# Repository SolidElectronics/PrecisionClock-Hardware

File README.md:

# PrecisionClock-Hardware
Alternate board designs for [mitxela/PrecisionClockMkII](https://github.com/mitxela/PrecisionClockMkII)

[0.56 inch x 18](/0.56%20inch%20x%2018) is a fully compatible version of the original design, but using the more readily available 0.56" displays.

[two row tenths v2](/two%20row%20tenths%20v2/) is a new design that requires modified firmware which you can get from [SolidElectronics/PrecisionClockMkII](https://github.com/SolidElectronics/PrecisionClockMkII).  That firmware supports both the original and new board versions (select using the #define statements).  The major changes included in this board are:

- Stacked date above time.  Date uses 0.56" LEDs and time uses 0.8" LEDs with 3mm LEDs for colons.

- USB-C power input, with footprints for mounting the connector on the side or the bottom.

- Dedicated holes for antenna mount, and I included STLs for the common ceramic antenna included with the GPS modules, and an SMA-mount if you'd prefer to use that.  I also added optional covers that can go over the colon indicators to make it look a bit more finished.

- Use surface-mount components wherever possible (not the AVR or MAX7219s because I already had the DIP versions)

- Switched non-segment indicators (colons and GMT/BST indicators) to use dedicated output pins on the MCU.  I found that driving anything other than the segments from the MAX7219 caused ghosting on the associated digits, and there wasn't a way to reduce the LED brightness that worked.

- Implemented digital brightness control.  The analog brightness control was great in theory but I couldn't get it to drive the LEDs at a level I was happy with, it would either be too bright or they'd go out entirely in a dark environment.  This probably could have been resolved by picking the correct transistors, LDR, and resistor values, but it was too much of a pain to re-solder them every time.

  Some concessions had to be made here due to the hardware limitations of the ATTiny2313, there is no ADC and only one available PWM output.  The LDR now uses the analog comparator to switch beteen high and low brightness, not a smooth gradient.  The non-segment indicators are PWM-driven through a 74AHCT125 so their brightness can be set independently from the main display, and the main display now uses the built-in dimming function from the MAX7219.  All of the parameters are tunable in the firmware, and there are potentiometers on the back to set the dimming switchover point and the overall date and time brightness levels.

It took a lot more work than I expected to get it to this point, and it was probably the most trace-dense board I've made, but overall I'm happy with how it turned out and it's now a permanent fixture in my office.

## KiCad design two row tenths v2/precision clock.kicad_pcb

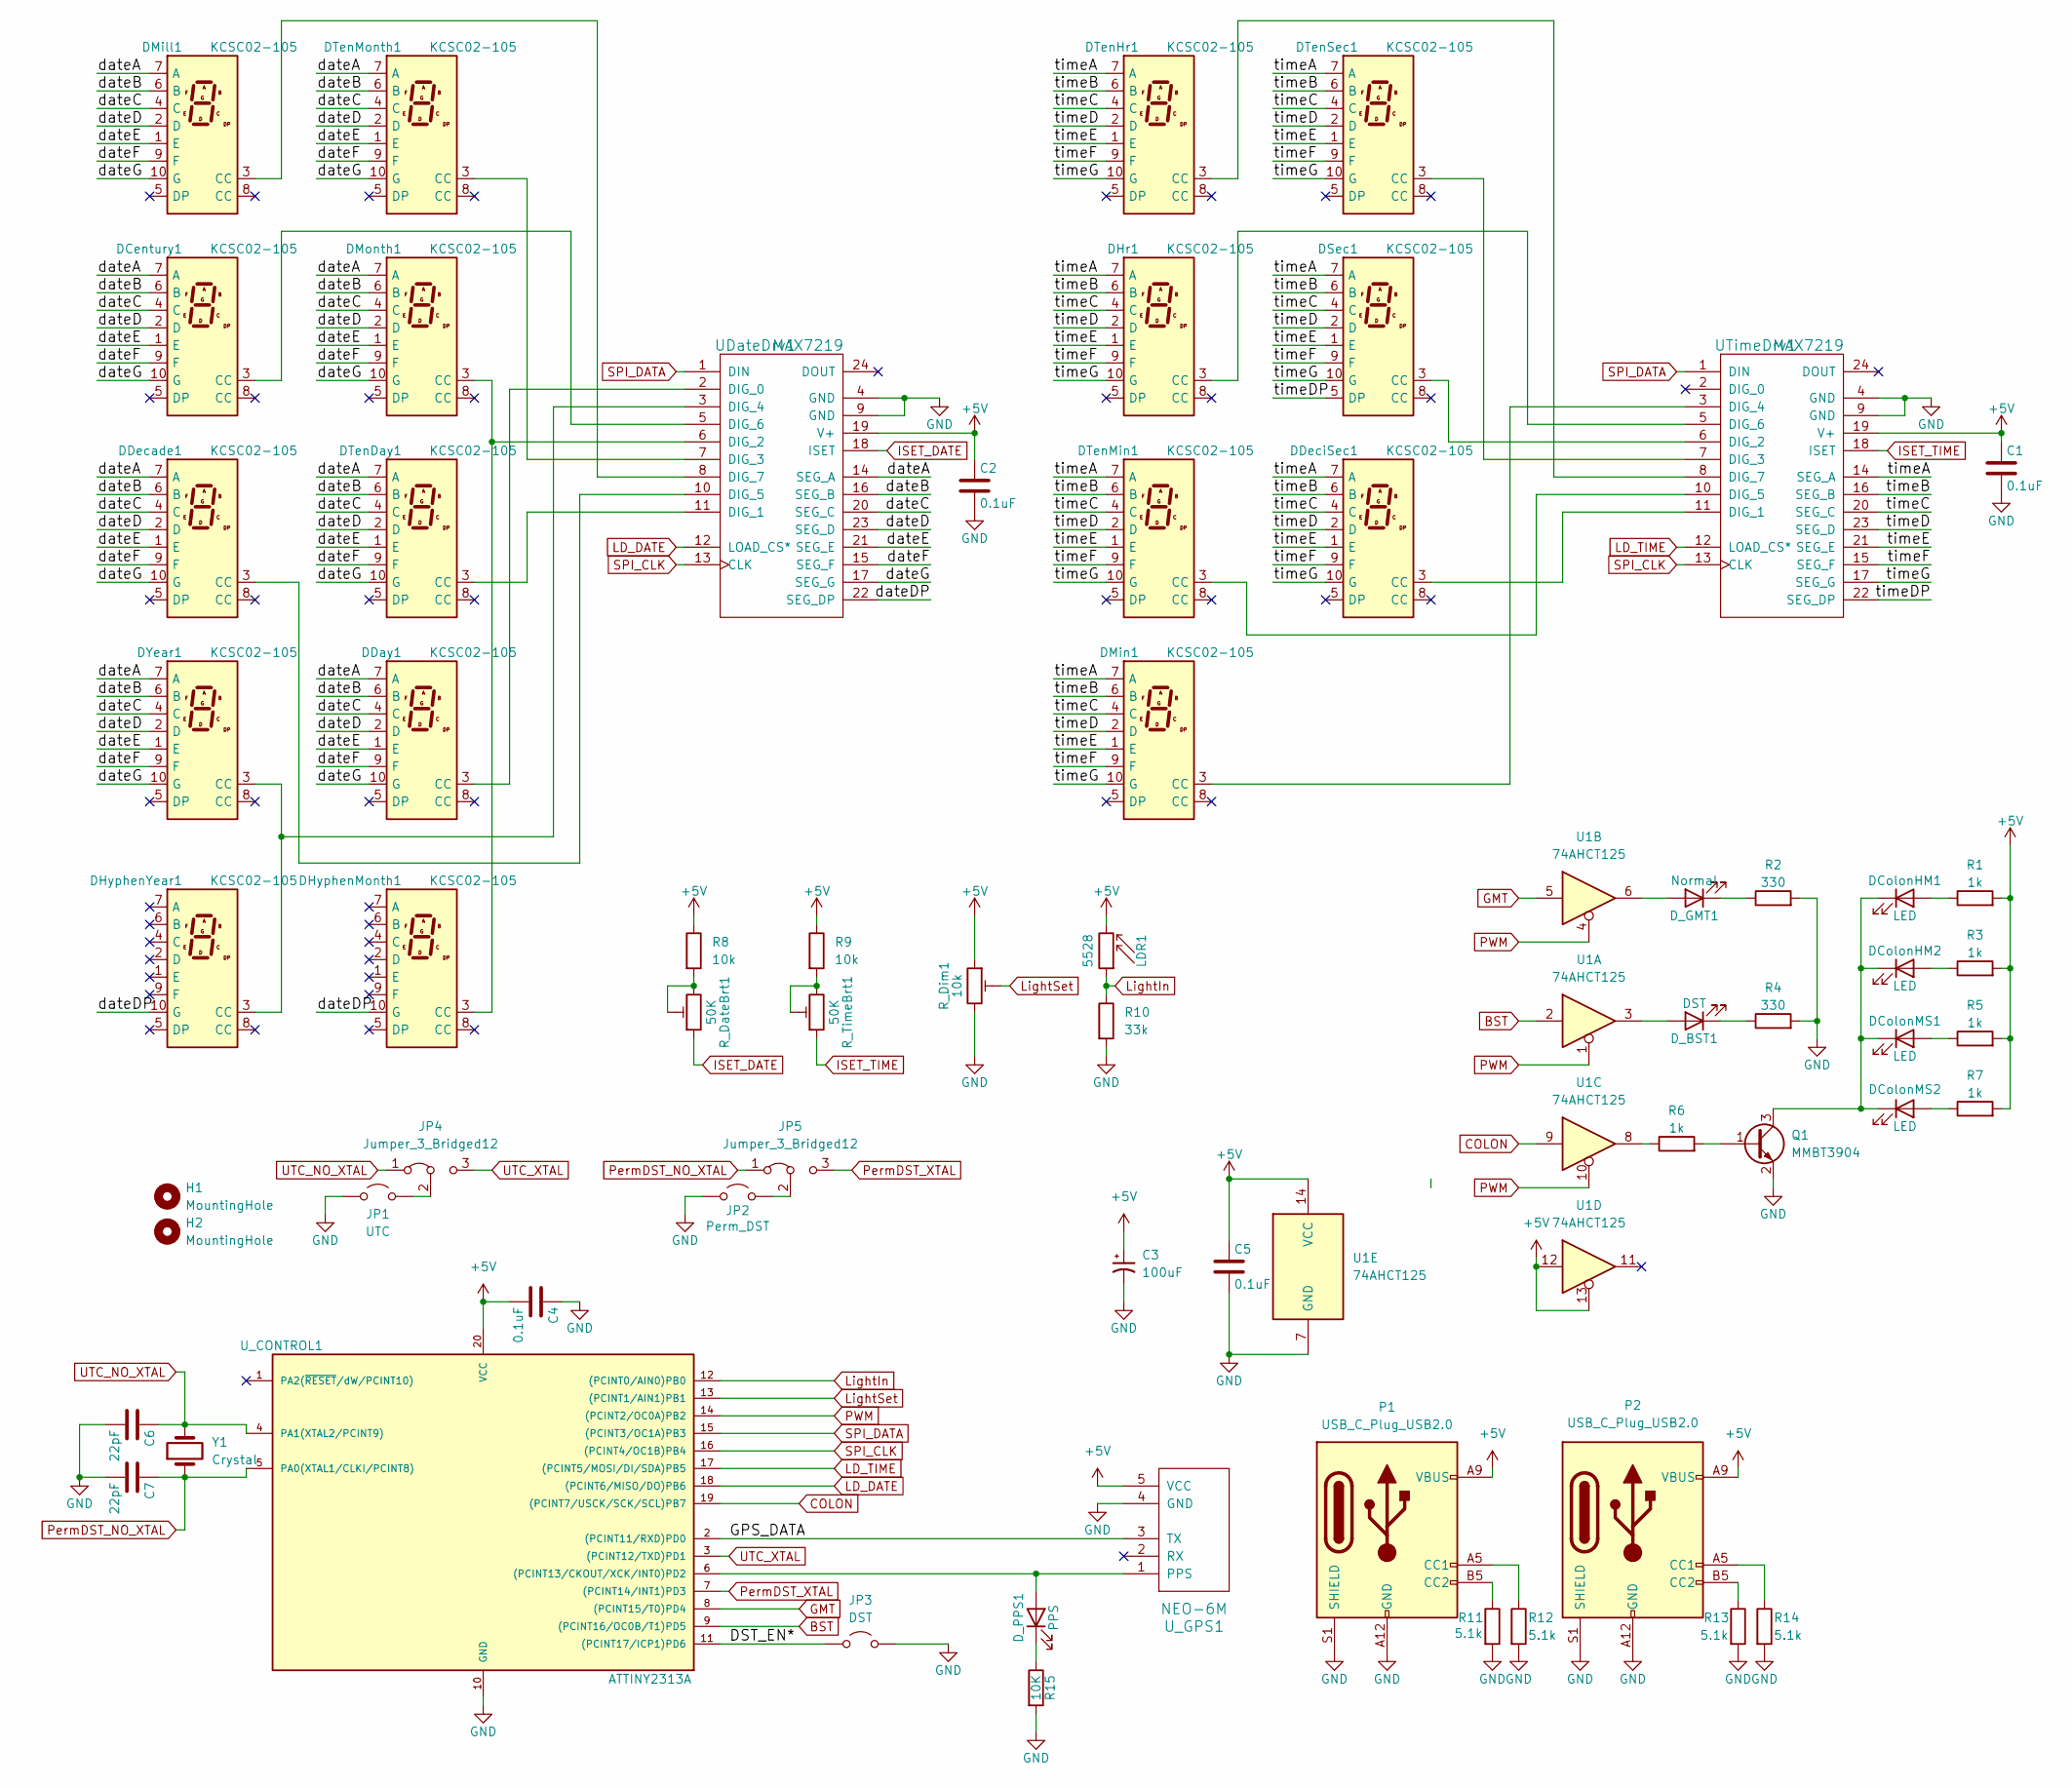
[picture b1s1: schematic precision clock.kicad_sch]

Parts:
C1, C2, C4, C5: 0.1uF; C_1206_3216Metric
C3: 100uF; CP_Radial_D6.3mm_P2.50mm
C6, C7: 22pF; C_1206_3216Metric
DCentury1: KCSC02-105; 7seg0.56CC
DColonHM1, DColonHM2: LED; LED_D5.0mm
DColonMS1, DColonMS2: LED; LED_D5.0mm
DDay1: KCSC02-105; 7seg0.56CC
DDecade1: KCSC02-105; 7seg0.56CC
DDeciSec1: KCSC02-105; 7seg0.8CC
DHr1: KCSC02-105; 7seg0.8CC
DHyphenMonth1: KCSC02-105; 7seg0.56CC
DHyphenYear1: KCSC02-105; 7seg0.56CC
DMill1: KCSC02-105; 7seg0.56CC
DMin1: KCSC02-105; 7seg0.8CC
DMonth1: KCSC02-105; 7seg0.56CC
DSec1: KCSC02-105; 7seg0.8CC
DTenDay1: KCSC02-105; 7seg0.56CC
DTenHr1: KCSC02-105; 7seg0.8CC
DTenMin1: KCSC02-105; 7seg0.8CC
DTenMonth1: KCSC02-105; 7seg0.56CC
DTenSec1: KCSC02-105; 7seg0.8CC
DYear1: KCSC02-105; 7seg0.56CC
D_BST1: DST; LED_1206_3216Metric
D_GMT1: Normal; LED_1206_3216Metric
D_PPS1: PPS; LED_1206_3216Metric
H1, H2: MountingHole; MountingHole_3.2mm_M3
JP1: UTC; PinHeader_1x02_P2.54mm_Vertical
JP2: Perm_DST; PinHeader_1x02_P2.54mm_Vertical
JP3: DST; PinHeader_1x02_P2.54mm_Vertical
JP4, JP5: Jumper_3_Bridged12; SolderJumper-3_P1.3mm_Bridged12_Pad1.0x1.5mm
LDR1: 5528; R_LDR_4.9x4.2mm_P2.54mm_Vertical
P1, P2: USB_C_Plug_USB2.0; USB_C_Receptacle_HRO_TYPE-C-31-M-17
Q1: MMBT3904; SOT-23
R1, R3, R5, R6, R7: 1k; R_1206_3216Metric
R2, R4: 330; R_1206_3216Metric
R8, R9: 10k; R_1206_3216Metric
R10: 33k; R_1206_3216Metric
R11, R12, R13, R14: 5.1k; R_1206_3216Metric
R15: 10K; R_1206_3216Metric
R_DateBrt1: 50K; Potentiometer_Piher_PT-6-V_Vertical
R_Dim1: 10k; Potentiometer_Piher_PT-6-V_Vertical
R_TimeBrt1: 50K; Potentiometer_Piher_PT-6-V_Vertical
U1: 74AHCT125; SOIC-14_3.9x8.7mm_P1.27mm
UDateDrv1: MAX7219; DIP-24_W7.62mm
UTimeDrv1: MAX7219; DIP-24_W7.62mm
U_CONTROL1: ATTINY2313A; DIP-20_W7.62mm
U_GPS1: NEO-6M; ublox_GPS
Y1: Crystal; Crystal_SMD_HC49-SD

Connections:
+5V: C1.1, C2.1, C3.1, C4.2, C5.1, LDR1.2, P1.A9 (VBUS), P1.B9 (VBUS), P2.A9 (VBUS), P2.B9 (VBUS), R1.2, R3.2, R5.2, R7.2, R8.1, R9.1, R_Dim1.1, U1.12, U1.13, U1.14 (VCC), UDateDrv1.19 (V+), UTimeDrv1.19 (V+), U_CONTROL1.20 (VCC), U_GPS1.5 (VCC)
/DST_EN*: JP3.1 (A), U_CONTROL1.11 ((PCINT17/ICP1)PD6)
/GPS_DATA: U_CONTROL1.2 ((PCINT11/RXD)PD0), U_GPS1.3 (TX)
/dateA: DCentury1.7 (A), DDay1.7 (A), DDecade1.7 (A), DMill1.7 (A), DMonth1.7 (A), DTenDay1.7 (A), DTenMonth1.7 (A), DYear1.7 (A), UDateDrv1.14 (SEG_A)
/dateB: DCentury1.6 (B), DDay1.6 (B), DDecade1.6 (B), DMill1.6 (B), DMonth1.6 (B), DTenDay1.6 (B), DTenMonth1.6 (B), DYear1.6 (B), UDateDrv1.16 (SEG_B)
/dateC: DCentury1.4 (C), DDay1.4 (C), DDecade1.4 (C), DMill1.4 (C), DMonth1.4 (C), DTenDay1.4 (C), DTenMonth1.4 (C), DYear1.4 (C), UDateDrv1.20 (SEG_C)
/dateD: DCentury1.2 (D), DDay1.2 (D), DDecade1.2 (D), DMill1.2 (D), DMonth1.2 (D), DTenDay1.2 (D), DTenMonth1.2 (D), DYear1.2 (D), UDateDrv1.23 (SEG_D)
/dateDP: DHyphenMonth1.10 (G), DHyphenYear1.10 (G), UDateDrv1.22 (SEG_DP)
/dateE: DCentury1.1 (E), DDay1.1 (E), DDecade1.1 (E), DMill1.1 (E), DMonth1.1 (E), DTenDay1.1 (E), DTenMonth1.1 (E), DYear1.1 (E), UDateDrv1.21 (SEG_E)
/dateF: DCentury1.9 (F), DDay1.9 (F), DDecade1.9 (F), DMill1.9 (F), DMonth1.9 (F), DTenDay1.9 (F), DTenMonth1.9 (F), DYear1.9 (F), UDateDrv1.15 (SEG_F)
/dateG: DCentury1.10 (G), DDay1.10 (G), DDecade1.10 (G), DMill1.10 (G), DMonth1.10 (G), DTenDay1.10 (G), DTenMonth1.10 (G), DYear1.10 (G), UDateDrv1.17 (SEG_G)
/timeA: DDeciSec1.7 (A), DHr1.7 (A), DMin1.7 (A), DSec1.7 (A), DTenHr1.7 (A), DTenMin1.7 (A), DTenSec1.7 (A), UTimeDrv1.14 (SEG_A)
/timeB: DDeciSec1.6 (B), DHr1.6 (B), DMin1.6 (B), DSec1.6 (B), DTenHr1.6 (B), DTenMin1.6 (B), DTenSec1.6 (B), UTimeDrv1.16 (SEG_B)
/timeC: DDeciSec1.4 (C), DHr1.4 (C), DMin1.4 (C), DSec1.4 (C), DTenHr1.4 (C), DTenMin1.4 (C), DTenSec1.4 (C), UTimeDrv1.20 (SEG_C)
/timeD: DDeciSec1.2 (D), DHr1.2 (D), DMin1.2 (D), DSec1.2 (D), DTenHr1.2 (D), DTenMin1.2 (D), DTenSec1.2 (D), UTimeDrv1.23 (SEG_D)
/timeDP: DSec1.5 (DP), UTimeDrv1.22 (SEG_DP)
/timeE: DDeciSec1.1 (E), DHr1.1 (E), DMin1.1 (E), DSec1.1 (E), DTenHr1.1 (E), DTenMin1.1 (E), DTenSec1.1 (E), UTimeDrv1.21 (SEG_E)
/timeF: DDeciSec1.9 (F), DHr1.9 (F), DMin1.9 (F), DSec1.9 (F), DTenHr1.9 (F), DTenMin1.9 (F), DTenSec1.9 (F), UTimeDrv1.15 (SEG_F)
/timeG: DDeciSec1.10 (G), DHr1.10 (G), DMin1.10 (G), DSec1.10 (G), DTenHr1.10 (G), DTenMin1.10 (G), DTenSec1.10 (G), UTimeDrv1.17 (SEG_G)
BST: U1.2, U_CONTROL1.9 ((PCINT16/OC0B/T1)PD5)
COLON: U1.9, U_CONTROL1.19 ((PCINT7/USCK/SCK/SCL)PB7)
GMT: U1.5, U_CONTROL1.8 ((PCINT15/T0)PD4)
GND: C1.2, C2.2, C3.2, C4.1, C5.2, C6.2, C7.2, JP1.2 (B), JP2.2 (B), JP3.2 (B), P1.A12 (GND), P1.B12 (GND), P1.S1 (SHIELD), P2.A12 (GND), P2.B12 (GND), P2.S1 (SHIELD), Q1.2 (E), R2.2, R4.2, R10.2, R11.2, R12.2, R13.2, R14.2, R15.2, R_Dim1.3, U1.7 (GND), UDateDrv1.4 (GND), UDateDrv1.9 (GND), UTimeDrv1.4 (GND), UTimeDrv1.9 (GND), U_CONTROL1.10 (GND), U_GPS1.4 (GND)
ISET_DATE: R_DateBrt1.1, UDateDrv1.18 (ISET)
ISET_TIME: R_TimeBrt1.1, UTimeDrv1.18 (ISET)
LD_DATE: UDateDrv1.12 (LOAD_CS*), U_CONTROL1.18 ((PCINT6/MISO/DO)PB6)
LD_TIME: UTimeDrv1.12 (LOAD_CS*), U_CONTROL1.17 ((PCINT5/MOSI/DI/SDA)PB5)
LightIn: LDR1.1, R10.1, U_CONTROL1.12 ((PCINT0/AIN0)PB0)
LightSet: R_Dim1.2, U_CONTROL1.13 ((PCINT1/AIN1)PB1)
unnamed: DColonHM1.2 (A), R1.1
unnamed: DColonHM1.1 (K), DColonHM2.1 (K), DColonMS1.1 (K), DColonMS2.1 (K), Q1.3 (C)
unnamed: DColonHM2.2 (A), R3.1
unnamed: DColonMS1.2 (A), R5.1
unnamed: DColonMS2.2 (A), R7.1
unnamed: D_BST1.2 (A), U1.3
unnamed: D_BST1.1 (K), R4.1
unnamed: D_GMT1.2 (A), U1.6
unnamed: D_GMT1.1 (K), R2.1
unnamed: D_PPS1.2 (A), U_CONTROL1.6 ((PCINT13/CKOUT/XCK/INT0)PD2), U_GPS1.1 (PPS)
unnamed: D_PPS1.1 (K), R15.1
unnamed: JP1.1 (A), JP4.2 (C)
unnamed: JP2.1 (A), JP5.2 (C)
unnamed: P1.A5 (CC1), R12.1
unnamed: P1.B5 (CC2), R11.1
unnamed: P2.A5 (CC1), R14.1
unnamed: P2.B5 (CC2), R13.1
unnamed: Q1.1 (B), R6.2
unnamed: R6.1, U1.8
unnamed: R8.2, R_DateBrt1.2, R_DateBrt1.3
unnamed: R9.2, R_TimeBrt1.2, R_TimeBrt1.3
unnamed: DDay1.3 (CC), UDateDrv1.2 (DIG_0)
unnamed: DTenDay1.3 (CC), UDateDrv1.11 (DIG_1)
unnamed: DHyphenMonth1.3 (CC), DMonth1.3 (CC), UDateDrv1.6 (DIG_2)
unnamed: DTenMonth1.3 (CC), UDateDrv1.7 (DIG_3)
unnamed: DHyphenYear1.3 (CC), DYear1.3 (CC), UDateDrv1.3 (DIG_4)
unnamed: DDecade1.3 (CC), UDateDrv1.10 (DIG_5)
unnamed: DCentury1.3 (CC), UDateDrv1.5 (DIG_6)
unnamed: DMill1.3 (CC), UDateDrv1.8 (DIG_7)
unnamed: DDeciSec1.3 (CC), UTimeDrv1.11 (DIG_1)
unnamed: DSec1.3 (CC), UTimeDrv1.6 (DIG_2)
unnamed: DTenSec1.3 (CC), UTimeDrv1.7 (DIG_3)
unnamed: DMin1.3 (CC), UTimeDrv1.3 (DIG_4)
unnamed: DTenMin1.3 (CC), UTimeDrv1.10 (DIG_5)
unnamed: DHr1.3 (CC), UTimeDrv1.5 (DIG_6)
unnamed: DTenHr1.3 (CC), UTimeDrv1.8 (DIG_7)
PWM: U1.1, U1.4, U1.10, U_CONTROL1.14 ((PCINT2/OC0A)PB2)
PermDST_NO_XTAL: C7.1, JP5.1 (A), U_CONTROL1.5 (PA0(XTAL1/CLKI/PCINT8)), Y1.1
PermDST_XTAL: JP5.3 (B), U_CONTROL1.7 ((PCINT14/INT1)PD3)
SPI_CLK: UDateDrv1.13 (CLK), UTimeDrv1.13 (CLK), U_CONTROL1.16 ((PCINT4/OC1B)PB4)
SPI_DATA: UDateDrv1.1 (DIN), UTimeDrv1.1 (DIN), U_CONTROL1.15 ((PCINT3/OC1A)PB3)
UTC_NO_XTAL: C6.1, JP4.1 (A), U_CONTROL1.4 (PA1(XTAL2/PCINT9)), Y1.2
UTC_XTAL: JP4.3 (B), U_CONTROL1.3 ((PCINT12/TXD)PD1)

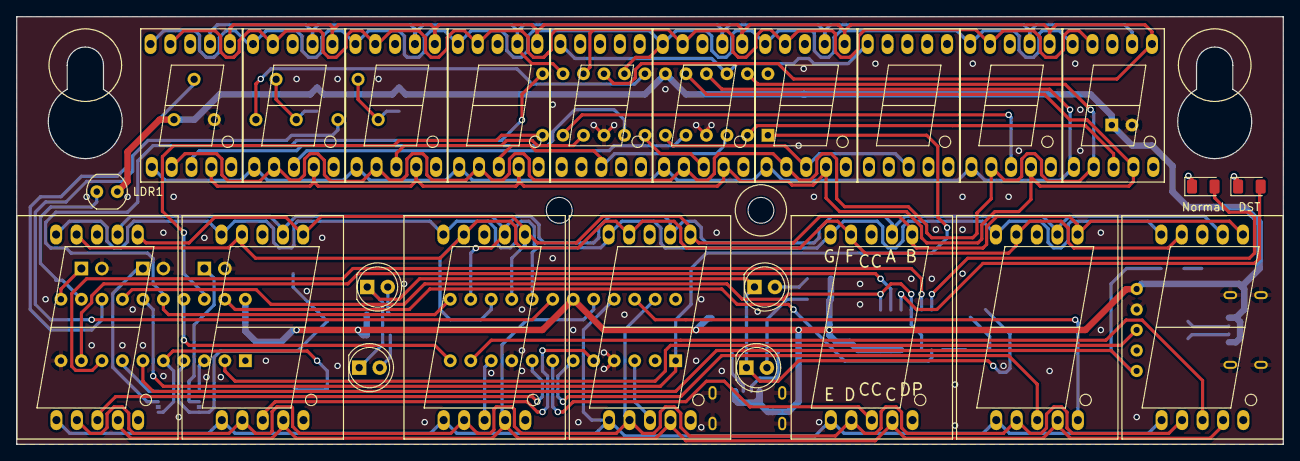
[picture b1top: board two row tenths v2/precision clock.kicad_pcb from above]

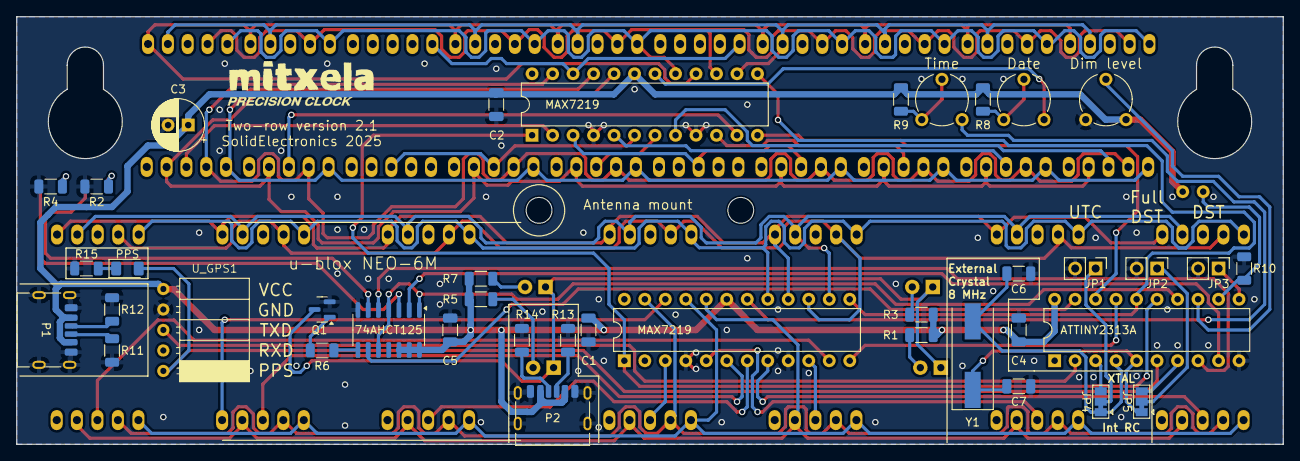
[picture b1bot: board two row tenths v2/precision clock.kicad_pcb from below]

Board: 2 copper layers, 157.0 x 53.0 mm, 66 parts (40 on the bottom side), 72 nets.

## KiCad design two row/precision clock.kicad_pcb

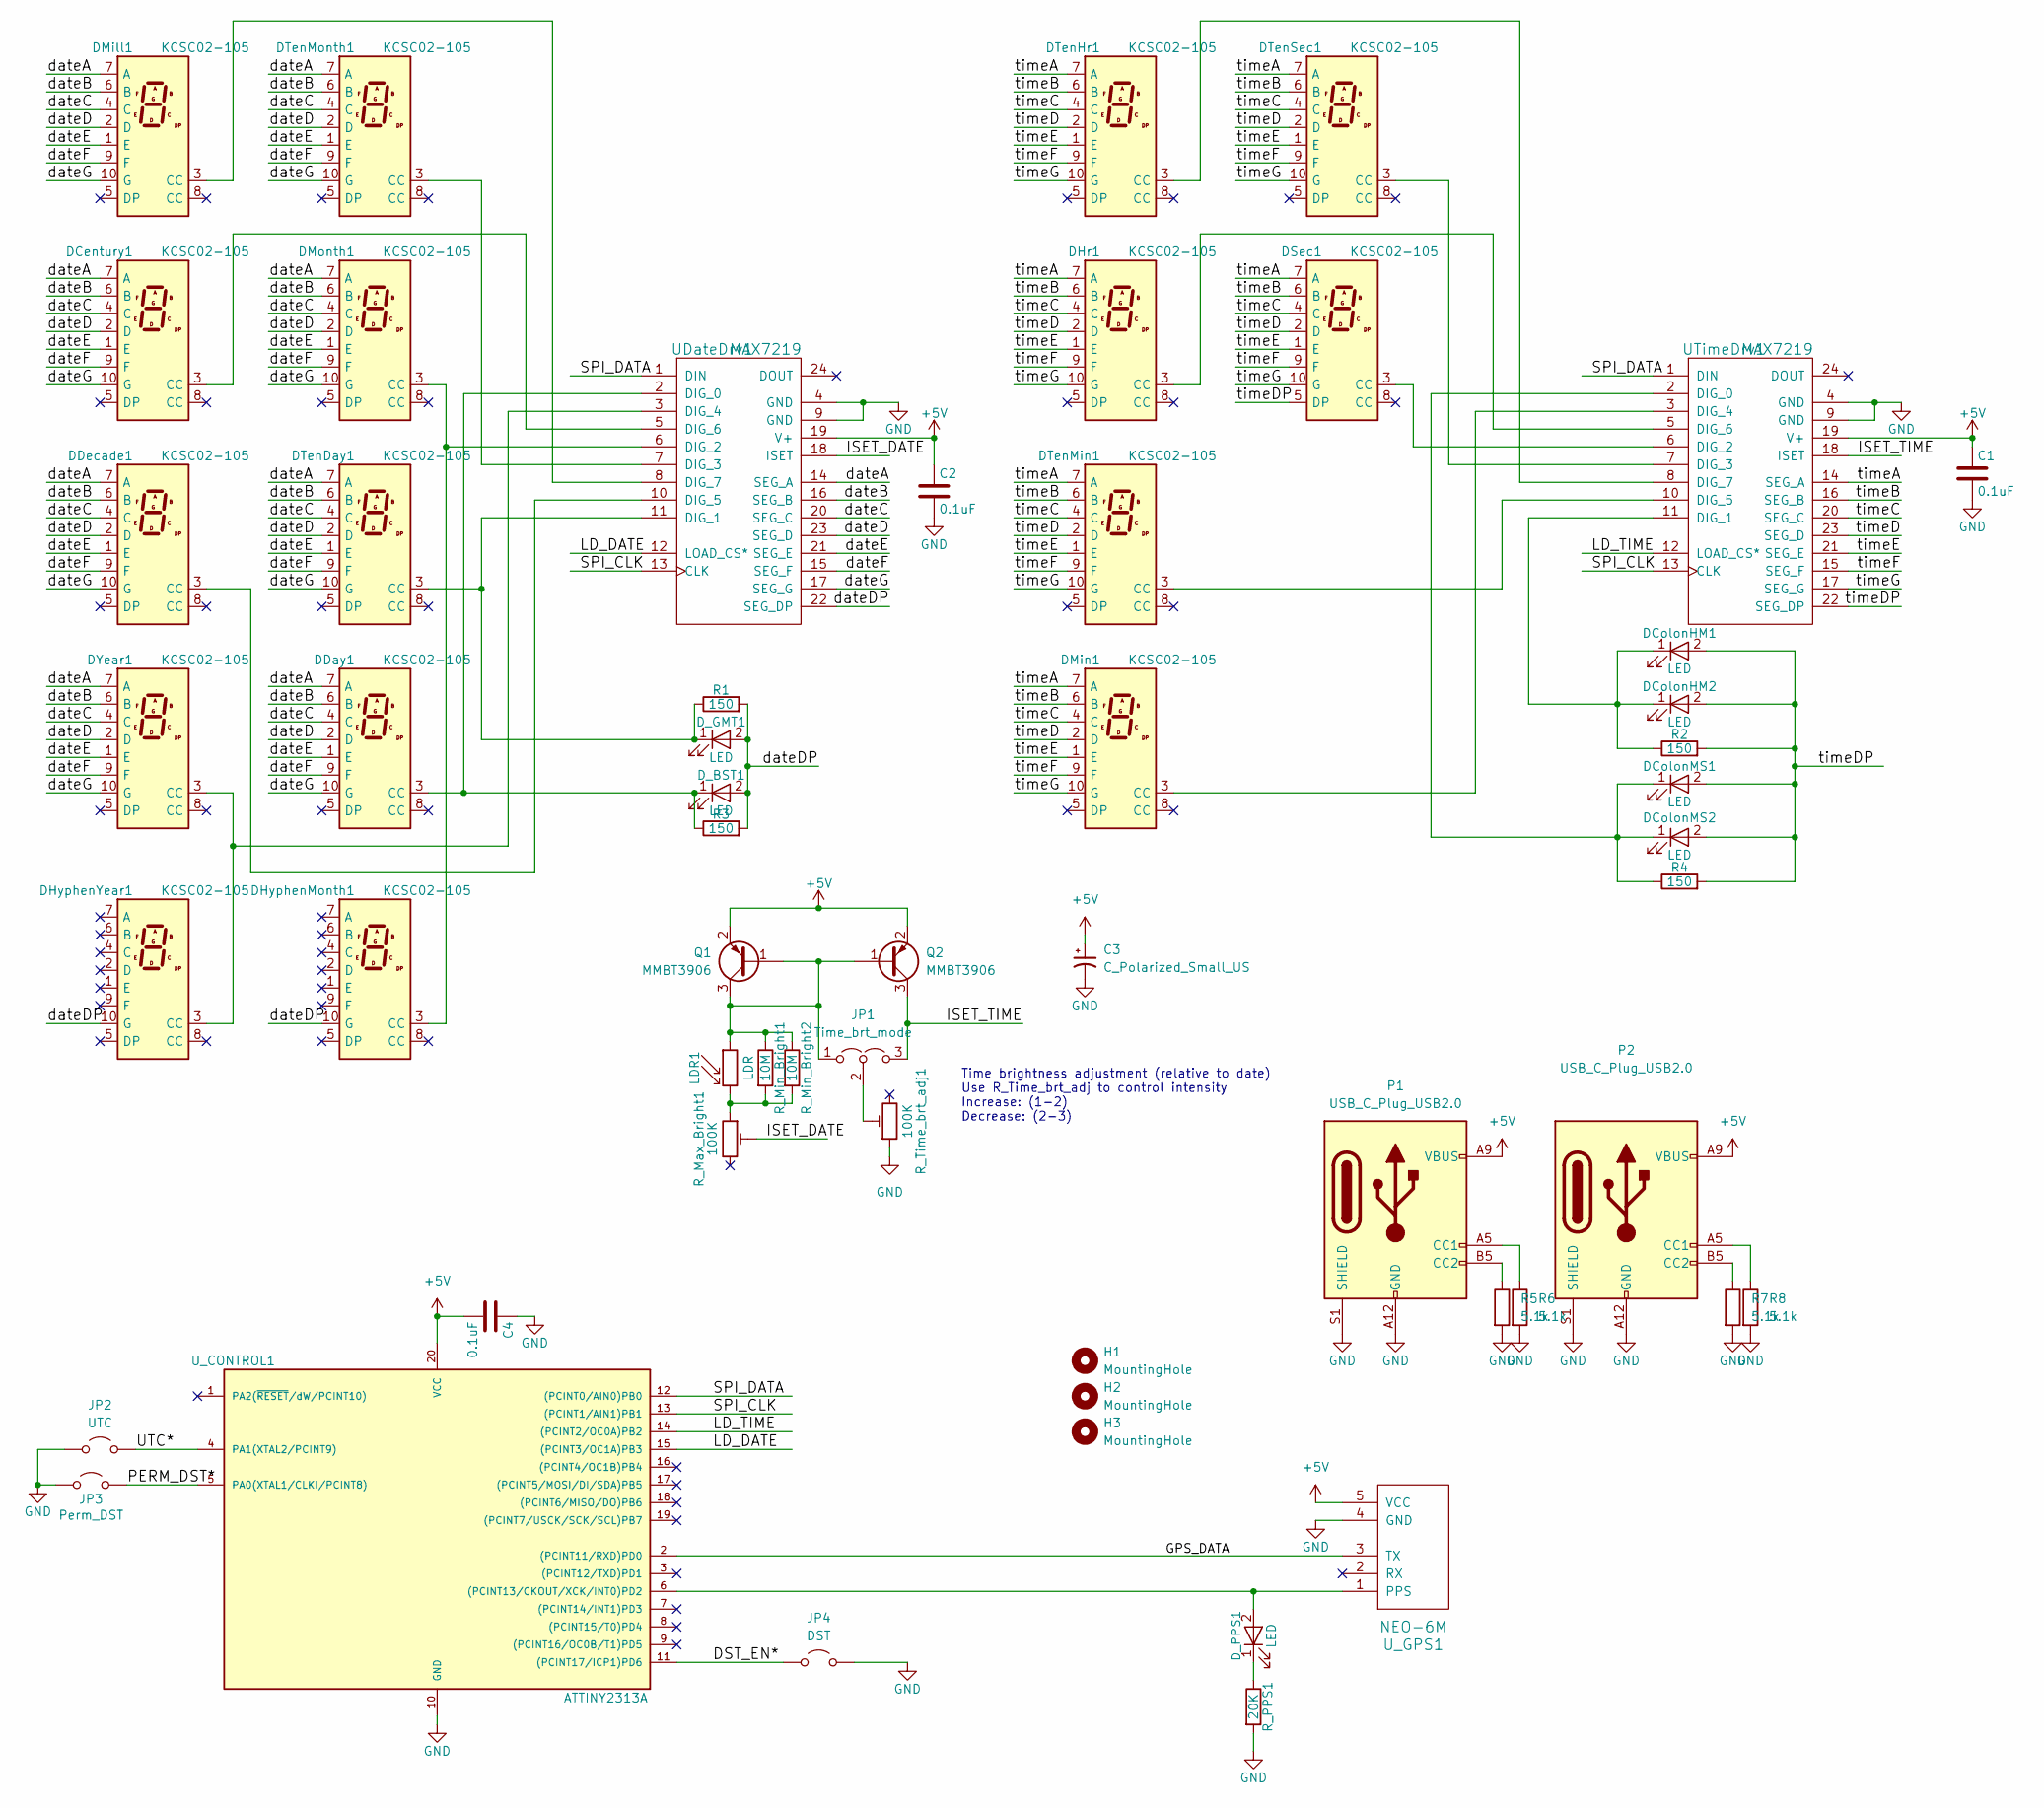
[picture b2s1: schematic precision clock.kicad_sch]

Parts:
C1, C2, C4: 0.1uF; C_1206_3216Metric
C3: C_Polarized_Small_US; CP_Radial_D5.0mm_P2.50mm
DCentury1: KCSC02-105; 7seg0.56CC
DColonHM1, DColonHM2: LED; LED_D5.0mm
DColonMS1, DColonMS2: LED; LED_D5.0mm
DDay1: KCSC02-105; 7seg0.56CC
DDecade1: KCSC02-105; 7seg0.56CC
DHr1: KCSC02-105; 7seg0.8CC
DHyphenMonth1: KCSC02-105; 7seg0.56CC
DHyphenYear1: KCSC02-105; 7seg0.56CC
DMill1: KCSC02-105; 7seg0.56CC
DMin1: KCSC02-105; 7seg0.8CC
DMonth1: KCSC02-105; 7seg0.56CC
DSec1: KCSC02-105; 7seg0.8CC
DTenDay1: KCSC02-105; 7seg0.56CC
DTenHr1: KCSC02-105; 7seg0.8CC
DTenMin1: KCSC02-105; 7seg0.8CC
DTenMonth1: KCSC02-105; 7seg0.56CC
DTenSec1: KCSC02-105; 7seg0.8CC
DYear1: KCSC02-105; 7seg0.56CC
D_BST1: LED; LED_1206_3216Metric
D_GMT1: LED; LED_1206_3216Metric
D_PPS1: LED; LED_1206_3216Metric
H1: MountingHole; MountingHole_3.2mm_M3
H2, H3: MountingHole; MountingHole_2mm
JP1: Time_brt_mode; PinHeader_1x03_P2.54mm_Vertical
JP2: UTC; PinHeader_1x02_P2.54mm_Vertical
JP3: Perm_DST; PinHeader_1x02_P2.54mm_Vertical
JP4: DST; PinHeader_1x02_P2.54mm_Vertical
LDR1: LDR; R_LDR_4.9x4.2mm_P2.54mm_Vertical
P1, P2: USB_C_Plug_USB2.0; USB_C_Receptacle_HRO_TYPE-C-31-M-17
Q1, Q2: MMBT3906; SOT-23
R1, R2, R3, R4: 150; R_1206_3216Metric
R5, R6, R7, R8: 5.1k; R_1206_3216Metric
R_Max_Bright1: 100K; Potentiometer_Piher_PT-6-V_Vertical
R_Min_Bright1: 10M; R_Axial_DIN0207_L6.3mm_D2.5mm_P7.62mm_Horizontal
R_Min_Bright2: 10M; R_1206_3216Metric
R_PPS1: 20K; R_1206_3216Metric
R_Time_brt_adj1: 100K; Potentiometer_Piher_PT-6-V_Vertical
UDateDrv1: MAX7219; DIP-24_W7.62mm
UTimeDrv1: MAX7219; DIP-24_W7.62mm
U_CONTROL1: ATTINY2313A; DIP-20_W7.62mm
U_GPS1: NEO-6M; PinSocket_1x05_P2.54mm_Horizontal

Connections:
+5V: C1.1, C2.1, C3.1, C4.2, P1.A9 (VBUS), P1.B9 (VBUS), P2.A9 (VBUS), P2.B9 (VBUS), Q1.2 (E), Q2.2 (E), UDateDrv1.19 (V+), UTimeDrv1.19 (V+), U_CONTROL1.20 (VCC), U_GPS1.5 (VCC)
/DST_EN*: JP4.1 (A), U_CONTROL1.11 ((PCINT17/ICP1)PD6)
/GPS_DATA: U_CONTROL1.2 ((PCINT11/RXD)PD0), U_GPS1.3 (TX)
/ISET_DATE: R_Max_Bright1.2, UDateDrv1.18 (ISET)
/ISET_TIME: JP1.3 (B), Q2.3 (C), UTimeDrv1.18 (ISET)
/LD_DATE: UDateDrv1.12 (LOAD_CS*), U_CONTROL1.15 ((PCINT3/OC1A)PB3)
/LD_TIME: UTimeDrv1.12 (LOAD_CS*), U_CONTROL1.14 ((PCINT2/OC0A)PB2)
/PERM_DST*: JP3.1 (A), U_CONTROL1.5 (PA0(XTAL1/CLKI/PCINT8))
/SPI_CLK: UDateDrv1.13 (CLK), UTimeDrv1.13 (CLK), U_CONTROL1.13 ((PCINT1/AIN1)PB1)
/SPI_DATA: UDateDrv1.1 (DIN), UTimeDrv1.1 (DIN), U_CONTROL1.12 ((PCINT0/AIN0)PB0)
/UTC*: JP2.1 (A), U_CONTROL1.4 (PA1(XTAL2/PCINT9))
/dateA: DCentury1.7 (A), DDay1.7 (A), DDecade1.7 (A), DMill1.7 (A), DMonth1.7 (A), DTenDay1.7 (A), DTenMonth1.7 (A), DYear1.7 (A), UDateDrv1.14 (SEG_A)
/dateB: DCentury1.6 (B), DDay1.6 (B), DDecade1.6 (B), DMill1.6 (B), DMonth1.6 (B), DTenDay1.6 (B), DTenMonth1.6 (B), DYear1.6 (B), UDateDrv1.16 (SEG_B)
/dateC: DCentury1.4 (C), DDay1.4 (C), DDecade1.4 (C), DMill1.4 (C), DMonth1.4 (C), DTenDay1.4 (C), DTenMonth1.4 (C), DYear1.4 (C), UDateDrv1.20 (SEG_C)
/dateD: DCentury1.2 (D), DDay1.2 (D), DDecade1.2 (D), DMill1.2 (D), DMonth1.2 (D), DTenDay1.2 (D), DTenMonth1.2 (D), DYear1.2 (D), UDateDrv1.23 (SEG_D)
/dateDP: DHyphenMonth1.10 (G), DHyphenYear1.10 (G), D_BST1.2 (A), D_GMT1.2 (A), R1.2, R3.2, UDateDrv1.22 (SEG_DP)
/dateE: DCentury1.1 (E), DDay1.1 (E), DDecade1.1 (E), DMill1.1 (E), DMonth1.1 (E), DTenDay1.1 (E), DTenMonth1.1 (E), DYear1.1 (E), UDateDrv1.21 (SEG_E)
/dateF: DCentury1.9 (F), DDay1.9 (F), DDecade1.9 (F), DMill1.9 (F), DMonth1.9 (F), DTenDay1.9 (F), DTenMonth1.9 (F), DYear1.9 (F), UDateDrv1.15 (SEG_F)
/dateG: DCentury1.10 (G), DDay1.10 (G), DDecade1.10 (G), DMill1.10 (G), DMonth1.10 (G), DTenDay1.10 (G), DTenMonth1.10 (G), DYear1.10 (G), UDateDrv1.17 (SEG_G)
/timeA: DHr1.7 (A), DMin1.7 (A), DSec1.7 (A), DTenHr1.7 (A), DTenMin1.7 (A), DTenSec1.7 (A), UTimeDrv1.14 (SEG_A)
/timeB: DHr1.6 (B), DMin1.6 (B), DSec1.6 (B), DTenHr1.6 (B), DTenMin1.6 (B), DTenSec1.6 (B), UTimeDrv1.16 (SEG_B)
/timeC: DHr1.4 (C), DMin1.4 (C), DSec1.4 (C), DTenHr1.4 (C), DTenMin1.4 (C), DTenSec1.4 (C), UTimeDrv1.20 (SEG_C)
/timeD: DHr1.2 (D), DMin1.2 (D), DSec1.2 (D), DTenHr1.2 (D), DTenMin1.2 (D), DTenSec1.2 (D), UTimeDrv1.23 (SEG_D)
/timeDP: DColonHM1.2 (A), DColonHM2.2 (A), DColonMS1.2 (A), DColonMS2.2 (A), DSec1.5 (DP), R2.2, R4.2, UTimeDrv1.22 (SEG_DP)
/timeE: DHr1.1 (E), DMin1.1 (E), DSec1.1 (E), DTenHr1.1 (E), DTenMin1.1 (E), DTenSec1.1 (E), UTimeDrv1.21 (SEG_E)
/timeF: DHr1.9 (F), DMin1.9 (F), DSec1.9 (F), DTenHr1.9 (F), DTenMin1.9 (F), DTenSec1.9 (F), UTimeDrv1.15 (SEG_F)
/timeG: DHr1.10 (G), DMin1.10 (G), DSec1.10 (G), DTenHr1.10 (G), DTenMin1.10 (G), DTenSec1.10 (G), UTimeDrv1.17 (SEG_G)
GND: C1.2, C2.2, C3.2, C4.1, JP2.2 (B), JP3.2 (B), JP4.2 (B), P1.A12 (GND), P1.B12 (GND), P1.S1 (SHIELD), P2.A12 (GND), P2.B12 (GND), P2.S1 (SHIELD), R5.2, R6.2, R7.2, R8.2, R_PPS1.2, R_Time_brt_adj1.1, UDateDrv1.4 (GND), UDateDrv1.9 (GND), UTimeDrv1.4 (GND), UTimeDrv1.9 (GND), U_CONTROL1.10 (GND), U_GPS1.4 (GND)
unnamed: DColonHM1.1 (K), DColonHM2.1 (K), R2.1, UTimeDrv1.11 (DIG_1)
unnamed: DColonMS1.1 (K), DColonMS2.1 (K), R4.1, UTimeDrv1.2 (DIG_0)
unnamed: DDay1.3 (CC), D_BST1.1 (K), R3.1, UDateDrv1.2 (DIG_0)
unnamed: DTenDay1.3 (CC), D_GMT1.1 (K), R1.1, UDateDrv1.11 (DIG_1)
unnamed: D_PPS1.2 (A), U_CONTROL1.6 ((PCINT13/CKOUT/XCK/INT0)PD2), U_GPS1.1 (PPS)
unnamed: D_PPS1.1 (K), R_PPS1.1
unnamed: JP1.1 (A), LDR1.1, Q1.1 (B), Q1.3 (C), Q2.1 (B), R_Min_Bright1.1, R_Min_Bright2.1
unnamed: JP1.2 (C), R_Time_brt_adj1.2
unnamed: LDR1.2, R_Max_Bright1.1, R_Min_Bright1.2, R_Min_Bright2.2
unnamed: P1.A5 (CC1), R6.1
unnamed: P1.B5 (CC2), R5.1
unnamed: P2.A5 (CC1), R8.1
unnamed: P2.B5 (CC2), R7.1
unnamed: DHyphenMonth1.3 (CC), DMonth1.3 (CC), UDateDrv1.6 (DIG_2)
unnamed: DTenMonth1.3 (CC), UDateDrv1.7 (DIG_3)
unnamed: DHyphenYear1.3 (CC), DYear1.3 (CC), UDateDrv1.3 (DIG_4)
unnamed: DDecade1.3 (CC), UDateDrv1.10 (DIG_5)
unnamed: DCentury1.3 (CC), UDateDrv1.5 (DIG_6)
unnamed: DMill1.3 (CC), UDateDrv1.8 (DIG_7)
unnamed: DSec1.3 (CC), UTimeDrv1.6 (DIG_2)
unnamed: DTenSec1.3 (CC), UTimeDrv1.7 (DIG_3)
unnamed: DMin1.3 (CC), UTimeDrv1.3 (DIG_4)
unnamed: DTenMin1.3 (CC), UTimeDrv1.10 (DIG_5)
unnamed: DHr1.3 (CC), UTimeDrv1.5 (DIG_6)
unnamed: DTenHr1.3 (CC), UTimeDrv1.8 (DIG_7)

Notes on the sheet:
Time brightness adjustment (relative to date) Use R_Time_brt_adj to control intensity Increase: (1-2) Decrease: (2-3)

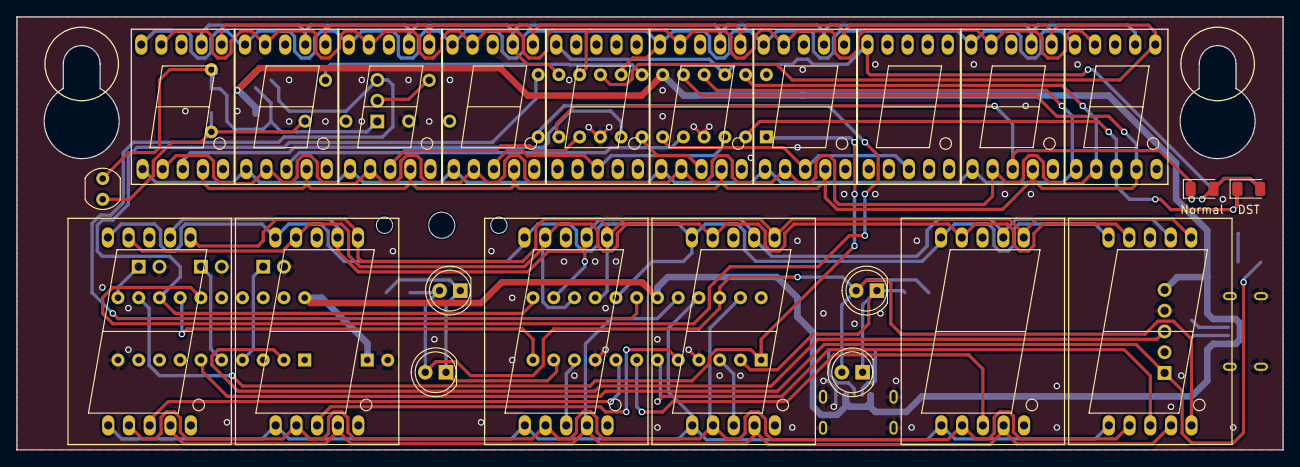
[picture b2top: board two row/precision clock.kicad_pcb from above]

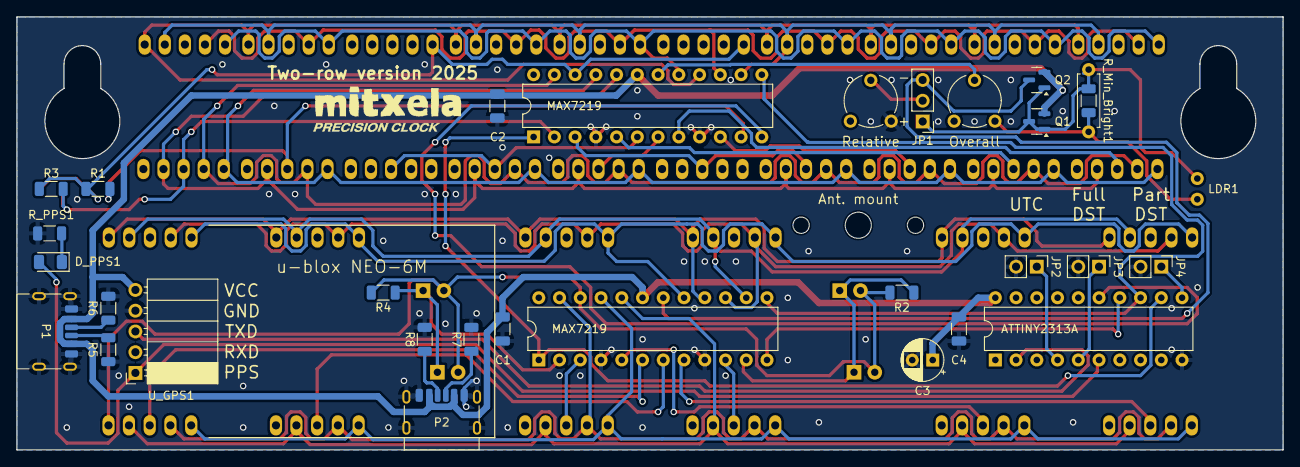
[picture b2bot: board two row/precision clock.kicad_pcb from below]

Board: 2 copper layers, 155.0 x 53.0 mm, 56 parts (30 on the bottom side), 53 nets.

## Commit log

2025-03-01 0.56" version v1
2025-03-02 Add new schematic format
2025-03-02 Cleanup rescue files
2025-03-02 Add jumpers for permaDST and UTC
2025-03-05 Move 0.56" into new folder
2025-03-05 Create new layout for two rows, 1" time and 0.56" date
2025-03-05 Cleanup base dir
2025-03-13 Rebuild two-row for 0.8" segments and improvements from prototype (1.0" are very difficult to source)
2025-03-17 Remove extra resistors, add second USB port location, cleanup trace routing
2025-03-19 Add wire to seconds decimal point
2025-03-22 Fixed USB-C pinout and CC resistors
2025-03-23 Fix reference designators
2025-03-23 Add new two-row version including tenth second digit
2025-03-23 Move over bottom USB connector
2025-04-03 Add resistor so we don't short Q2
2025-04-04 More resistors for brightness tuning
2025-04-07 Add new version with MCU driven colons and digital dimming, fixing problems found in version 1.
2025-04-09 Add 74AHCT125 as PWM driver
2025-04-09 Add optional crystal
2025-04-09 Add GPS model, sending to production.
2025-04-22 Fix LED polarity, add STLs for antenna mounts
2025-04-23 Cleanup old projects
2025-04-27 Added README.md
